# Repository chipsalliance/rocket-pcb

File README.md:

# ROCKET PCB

This project includes the following sub-projects, please read the relevant
documents of sub-projects carefully before starting to use the corresponding
projects.

## FPGA

|            PROJECT         |                     INTRODUCTION                  |
| -------------------------- | ------------------------------------------------- |
| [FPGA_CANDELABRA](./fpga_candelabra) | XCVU13P development board with DDR4, FMC and PCIE |

## FMC

|                 PROJECT                  |          INTRODUCTION          |
| ---------------------------------------- | ------------------------------ |
| [FMC_BASIC_PERI](./fmc_basic_peripheral) | JTAG, UART, GPIO, USB, I3C FMC |
| [FMC_SDRAM](./fmc_sdram)                 | FMC of SDRAM and JTAG          |

## PMOD

|            PROJECT             |      INTRODUCTION      |
| ------------------------------ | ---------------------- |
| [PMOD_MICROSD](./pmod_microsd) | PMOD microSD card slot |
| [PMOD_FT_LINK](./pmod_ft_link/README.md) | FT2232HL USB JTAG and UART adapter for 3.3 V Pmod GPIO ports |

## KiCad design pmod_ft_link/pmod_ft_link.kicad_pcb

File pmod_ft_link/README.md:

# PMOD_FT_LINK

FT-LINK is a USB-to-JTAG and UART adapter built around the FT2232HL. It
connects to a 12-pin Pmod GPIO port with 3.3 V logic. Channel A provides
JTAG through MPSSE; channel B provides UART.

**Keep JP1, marked TIE on the back, open when the host supplies Pmod power.**
The adapter has fixed 3.3 V I/O; it does not sense the target voltage or
translate logic levels. Power the target before driving its signal pins.

## 3D view

### Top view

### Bottom view

## Introduction

### Pmod

The board uses the mechanical dimensions, connector pitch and power-pin
positions of the [Pmod Interface Specification 1.2.0](https://digilent.com/reference/_media/reference/pmod/pmod-interface-specification-1_2_0.pdf).
Its outline is 36.00 × 20.32 mm, with a 1.6 mm thick, two-layer PCB and a
right-angle male connector on 2.54 mm pitch. Specify black solder mask and
white silkscreen on both sides when ordering.

The GPIO assignments below are specific to FT-LINK. This is not an ARM
20-pin or Cortex 10-pin JTAG connector. The FPGA pin constraints and debug
software must use this mapping; a Pmod GPIO port does not automatically
connect to the FPGA's dedicated configuration JTAG chain.

Pmod numbers each six-pin row consecutively. The original FT-LINK drawing
and the VCU118 documentation use alternating odd/even numbering for the
same physical contacts:

| Pmod pin | Original / VCU118 pin | Signal | Direction at FT-LINK | FT2232HL pin |
| --- | --- | --- | --- | --- |
| 1 | 1 | TDO | Input | 18, ADBUS2 |
| 2 | 3 | NTRST | Output, active low | 26, ACBUS0 |
| 3 | 5 | TCK | Output | 16, ADBUS0 |
| 4 | 7 | RXD | Input | 39, BDBUS1 |
| 5 | 9 | GND | Ground | |
| 6 | 11 | PMOD_VCC | Host power rail | |
| 7 | 2 | TDI | Output | 17, ADBUS1 |
| 8 | 4 | TMS | Output | 19, ADBUS3 |
| 9 | 6 | NSRST | Output, active low | 27, ACBUS1 |
| 10 | 8 | TXD | Output | 38, BDBUS0 |
| 11 | 10 | GND | Ground | |
| 12 | 12 | PMOD_VCC | Host power rail | |

Connect TXD to the target's RX input and RXD to its TX output. The JTAG
clock/data signals use the FT2232H MPSSE assignments; the Pmod contact order
is the original FT-LINK order.

### Power and TIE jumper

USB VBUS supplies the FT2232HL through the resettable fuse and AP2112K-3.3
regulator. Pmod pins 6 and 12 are power pins, not VTref inputs. They form the
separate `PMOD_VCC` net while JP1 is open.

JP1 is the original pair of complementary diagonal solder pads, previously
labelled R11 in the source schematic. It is not a resistor or a permanent
net tie. The KiCad symbol is `Jumper:SolderJumper_2_Open`; the custom footprint
is in `CHIPSAlliance_Jumper`. Its copper and stencil shapes follow the
original Gerbers. No component is fitted, so it is excluded from the BOM
and placement files and has no component 3D model.

Bridging JP1 with solder connects USB-derived 3.3 V to the Pmod power rail.
Leave it open for a separately powered host. Closing it requires a deliberate
single-supply arrangement and a verified current budget. An open jumper
isolates the power rails, but does not isolate the signal pins from an
unpowered target.

### Clock

Y1 retains the author's Murata `CSTNE12M0GH5C000R0` ceramic resonator
(LCSC `C2659460`): 12 MHz, 3.2 × 1.3 mm, with two built-in 33 pF capacitors.
There are no added external load capacitors. The `Device:Resonator` symbol
and the CHIPSAlliance footprint retain its three-terminal circuit and the
manufacturer's recommended lands.

Its ±0.07% (±700 ppm) initial tolerance is outside FTDI's recommended
±30 ppm crystal specification. Retaining the original circuit does not
establish compliance with that recommendation, nor prove it cannot work.
Confirm oscillator start-up, frequency over the intended operating range,
and USB operation on assembled hardware before production.

### LEDs

| Reference | Color | Marking / function |
| --- | --- | --- |
| D1 | Red | PWR, USB-derived 3.3 V present |
| D2 | White | TX, driven by FTDI RXLED# |
| D3 | White | RX, driven by FTDI TXLED# |
| D4 | Blue | JTAG, driven by ACBUS3 |

The original TX/RX silkscreen and LED wiring are retained. Their markings
use the opposite perspective to the FTDI RXLED#/TXLED# signal names. JTAG
LED behavior depends on the software's ACBUS3 configuration.

## Preparation

Install KiCad 10, CMake and Ninja, then initialize the pinned library:

```sh
git submodule update --init pmod_ft_link/library
cd pmod_ft_link
```

Open `pmod_ft_link.kicad_pro` in KiCad. The schematic fits one landscape A4
sheet and uses the project's CHIPSAlliance drawing template. Board text
uses embedded Titillium Web Regular; installing the font separately is not
required to view the saved design.

## Build

```sh
cmake -G Ninja -B build
cmake --build build
```

Individual targets are available:

```sh
cmake --build build --target erc drc
cmake --build build --target pdf
cmake --build build --target production
```

Production output contains two-layer Gerbers, separate plated/non-plated
drill files, BOM and SMT placement data. The drill/placement origin is the
lower-left board corner; bottom placement X is negated. Silkscreen export
subtracts solder-mask openings. Generated files stay under `build/`.

J1 is a hybrid USB connector with SMT contacts and plated shield slots;
J2 is through-hole. Both original component placement and signal routing
are retained apart from changes needed for the native footprints and Pmod
mechanics. J1's locating holes use a local 0.10 mm pad-to-hole clearance
matching its land pattern; routed copper retains 0.25 mm hole clearance.

Native DRC retains advisories for the original small regular-weight board
lettering, the intentional negative-text panel, and J1/J2 library-instance
silkscreen adjustments. The generic F1/J2 symbol footprint filters also
produce advisories. These are not hidden. ERC/DRC do not replace hardware
checks of the clock, USB signal integrity, power budget or target compatibility.

## Origin and licenses

Original designer: **-T.K.-**, `t_k_233@outlook.com`, UC Berkeley.
The design comes from [PR #2](https://github.com/chipsalliance/rocket-pcb/pull/2),
source commit `8a24312734b0e4b31bfd77401dffb280b939f82e`.
The title blocks retain the original schematic date **2024-02-29**, PCB date
**2024-03-20**, and revision **V2.0.0**.

The native KiCad migration preserves the circuit, artwork and clock choice,
uses standard or CHIPSAlliance library assets, and renames the solder bridge
from R11 to JP1. The original artwork remains editable vector geometry;
the board lettering uses native editable text. No EasyEDA source archives,
manufacturing outputs or review reports are required in this directory.

The source font name was `ACME Titillium Web Regular`. Board lettering now
uses the unmodified [Titillium Web Regular font from Google Fonts](https://github.com/google/fonts/tree/main/ofl/titilliumweb),
embedded in `pmod_ft_link.kicad_pcb`. Its copyright notice and full SIL Open
Font License 1.1 are in [licenses/TitilliumWeb-OFL.txt](./licenses/TitilliumWeb-OFL.txt).
The OFL permits commercial design use and embedding under its distribution
conditions. The ACME font binary is not redistributed. Library reference
and fabrication fields retain KiCad's default font, as required by KLC.

## References

- [FT2232H datasheet, oscillator section 6.3](https://ftdichip.com/wp-content/uploads/2024/05/DS_FT2232H.pdf)
- [Murata CSTNE12M0GH5C000R0 specification](https://www.murata.com/products/productdata/8801162100766/SPEC-CSTNE12M0GH5C000R0.pdf)
- [Kinghelm KH-TYPE-C-16P drawing](https://www.kinghelm.com.cn/upload/file/20220505/KH-TYPE-C-16P.pdf)

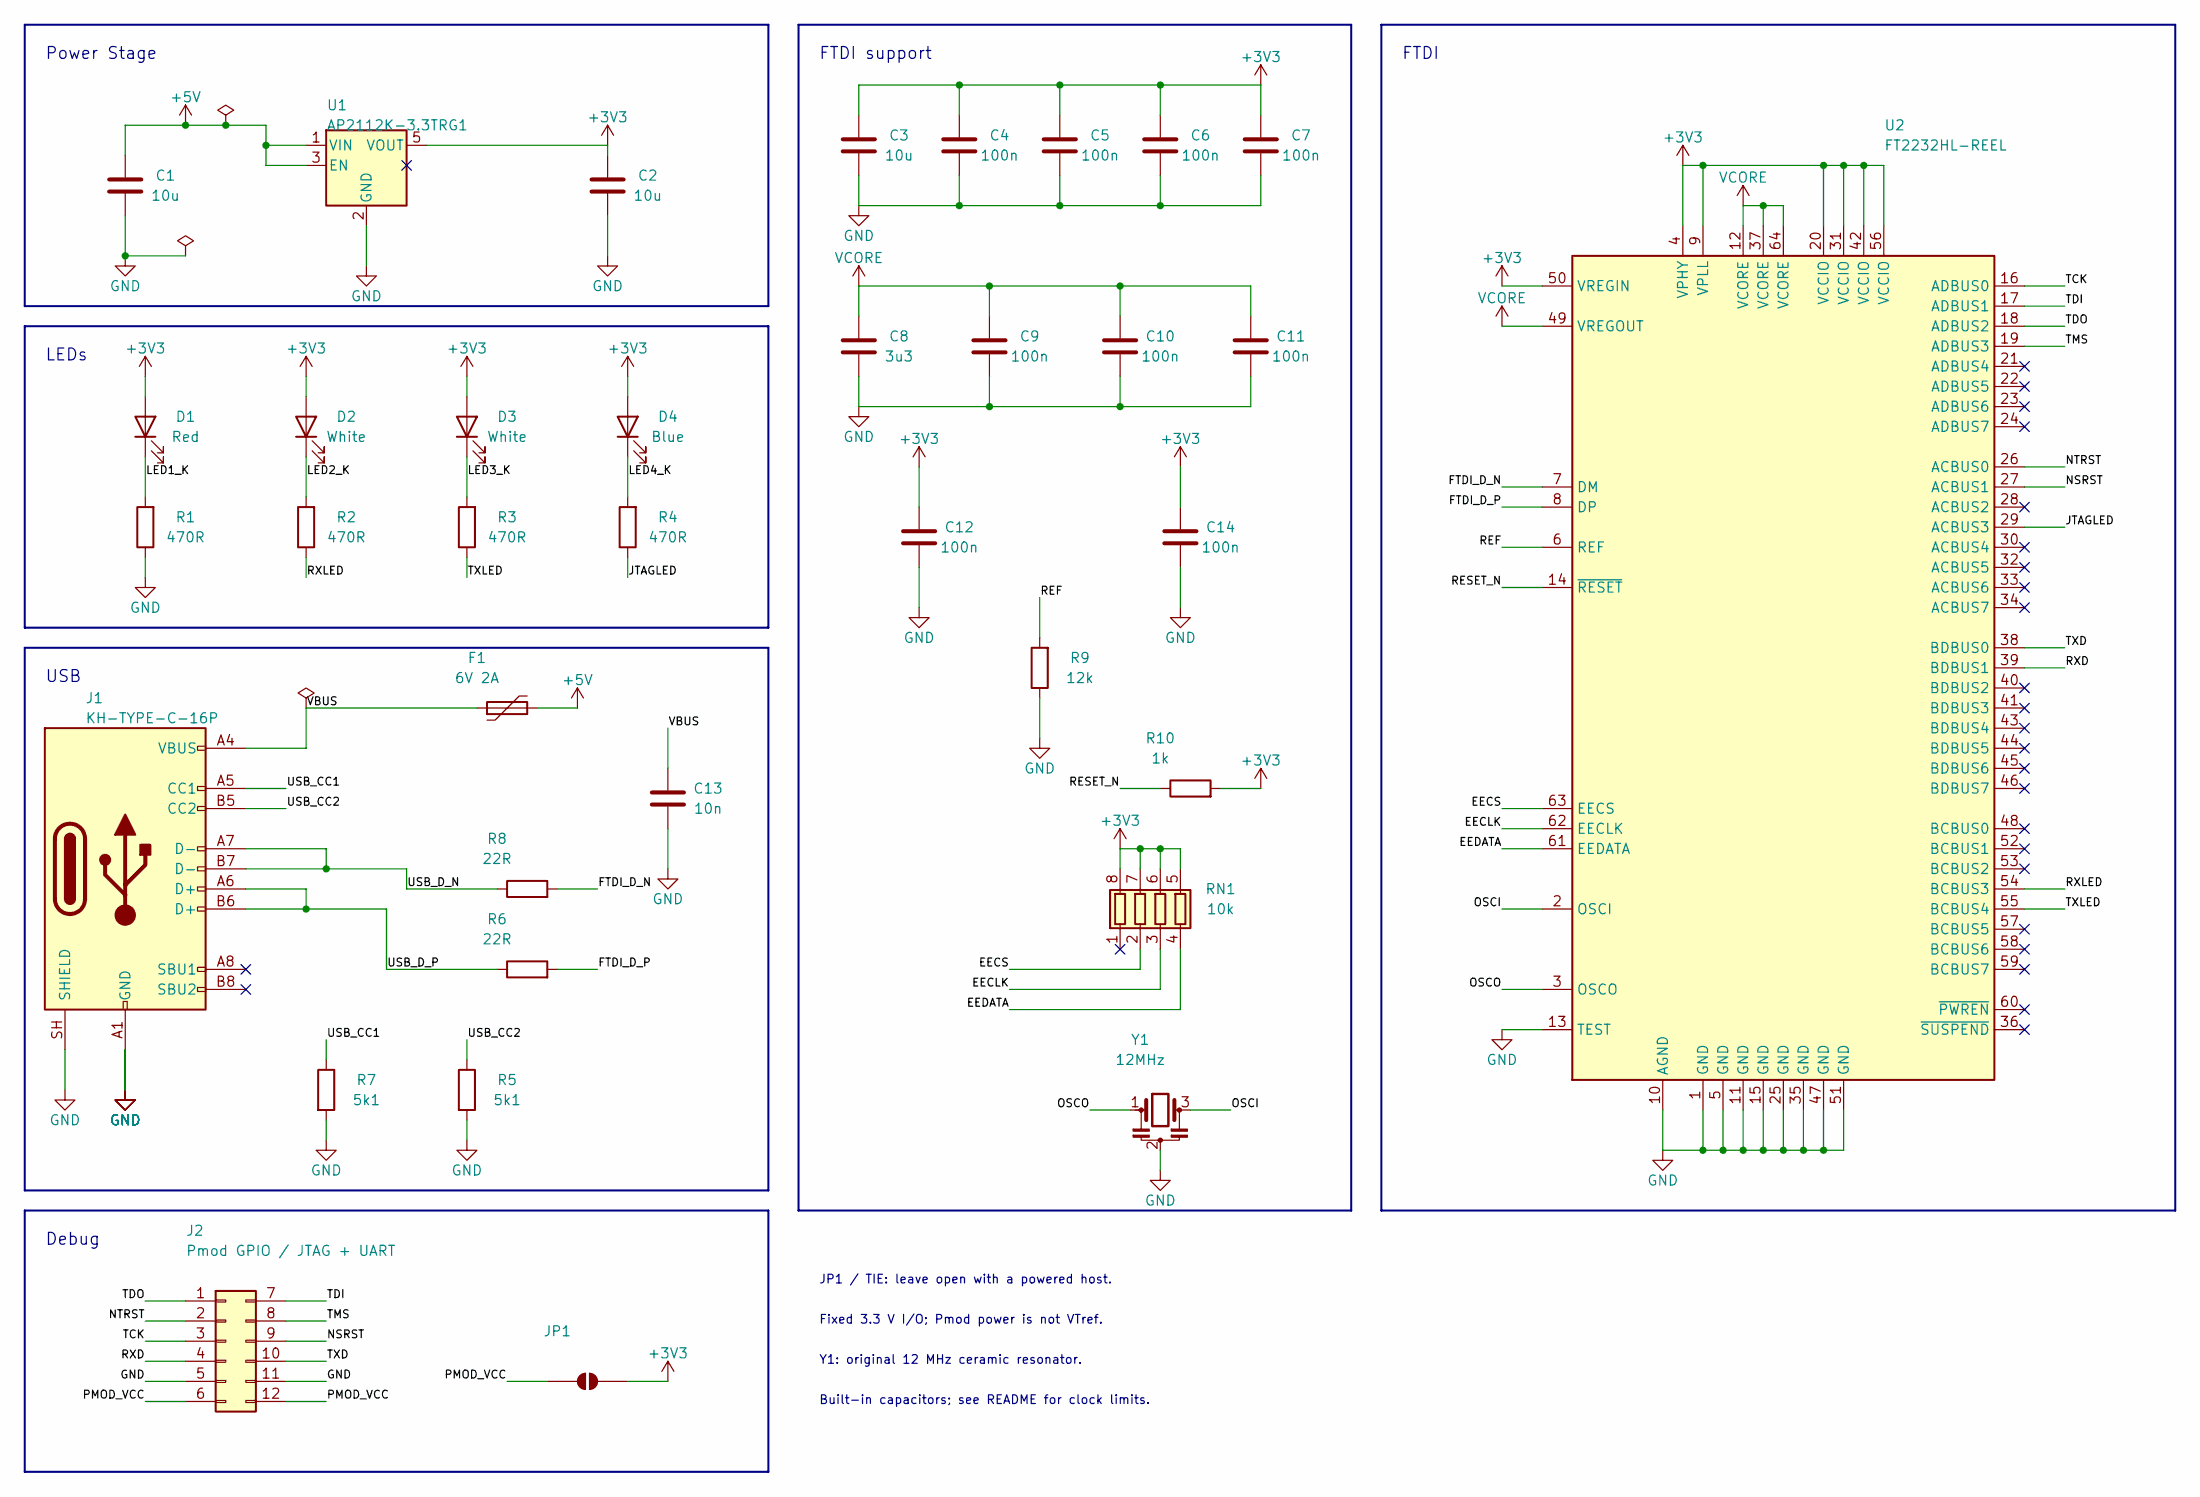
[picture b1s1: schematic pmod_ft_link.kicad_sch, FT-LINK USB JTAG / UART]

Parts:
C1, C2, C3: 10u; C_0603_1608Metric; MPN CL10A106KP8NNNC; LCSC C19702
C4, C5, C6, C7, C9, C10, C11, C12, C14: 100n; C_0402_1005Metric; MPN CL05B104KB54PNC; LCSC C307331
C8: 3u3; C_0603_1608Metric; MPN C1608X5R1E335KT000E; LCSC C342962
C13: 10n; C_0402_1005Metric; MPN CL05B103KB5NNNC; LCSC C15195
D1: Red; LED_0603_1608Metric; MPN 19-217/R6C-AL1M2VY/3T; LCSC C72044
D2, D3: White; LED_0603_1608Metric; MPN LED White; LCSC C2290
D4: Blue; LED_0603_1608Metric; MPN XL-0603QBC; LCSC C2288
F1: 6V 2A; Fuse_0805_2012Metric; MPN SL0805200; LCSC C70158
J1: KH-TYPE-C-16P; USB_C_Receptacle_Kinghelm_KH-TYPE-C-16P; MPN KH-TYPE-C-16P; LCSC C709357
J2: Pmod GPIO / JTAG + UART; PinHeader_2x06_P2.54mm_Horizontal_PMOD; MPN A2541WR-2x6P; LCSC C239337
JP1: SolderJumper_2_Open; SolderJumper-2_P0.713mm_Open_DiagonalPads
R1, R2, R3, R4: 470R; R_0402_1005Metric; MPN 0402WGF4700TCE; LCSC C25117
R5, R7: 5k1; R_0402_1005Metric; MPN 0402WGF5101TCE; LCSC C25905
R6, R8: 22R; R_0402_1005Metric; MPN 0402WGF220JTCE; LCSC C25092
R9: 12k; R_0402_1005Metric; MPN 0402WGF1202TCE; LCSC C25752
R10: 1k; R_0402_1005Metric; MPN 0402WGF1001TCE; LCSC C11702
RN1: 10k; R_Array_Convex_4x0402; MPN YC124-FR-0710KL; LCSC C136853
U1: AP2112K-3.3TRG1; SOT-23-5; MPN AP2112K-3.3TRG1; LCSC C51118
U2: FT2232HL-REEL; LQFP-64_10x10mm_P0.5mm; MPN FT2232HL-REEL; LCSC C27882
Y1: 12MHz; Resonator_SMD_Murata_CSTNE-3Pin_3.2x1.3mm; MPN CSTNE12M0GH5C000R0; LCSC C2659460

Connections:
+3V3: C2.2, C3.2, C4.2, C5.2, C6.2, C7.2, C12.2, C14.2, D1.2 (A), D2.2 (A), D3.2 (A), D4.2 (A), JP1.2 (B), R10.2, RN1.5 (R4.2), RN1.6 (R3.2), RN1.7 (R2.2), RN1.8 (R1.2), U1.5 (VOUT), U2.4 (VPHY), U2.9 (VPLL), U2.20 (VCCIO), U2.31 (VCCIO), U2.42 (VCCIO), U2.50 (VREGIN), U2.56 (VCCIO)
+5V: C1.2, F1.2, U1.1 (VIN), U1.3 (EN)
/EECLK: RN1.3 (R3.1), U2.62 (EECLK)
/EECS: RN1.2 (R2.1), U2.63 (EECS)
/EEDATA: RN1.4 (R4.1), U2.61 (EEDATA)
/FTDI_D_N: R8.2, U2.7 (DM)
/FTDI_D_P: R6.2, U2.8 (DP)
/JTAGLED: R4.1, U2.29 (ACBUS3)
/LED1_K: D1.1 (K), R1.2
/LED2_K: D2.1 (K), R2.2
/LED3_K: D3.1 (K), R3.2
/LED4_K: D4.1 (K), R4.2
/NSRST: J2.9, U2.27 (ACBUS1)
/NTRST: J2.2, U2.26 (ACBUS0)
/OSCI: U2.2 (OSCI), Y1.3
/OSCO: U2.3 (OSCO), Y1.1
/PMOD_VCC: J2.6, J2.12, JP1.1 (A)
/REF: R9.2, U2.6 (REF)
/RESET_N: R10.1, U2.14 (~RESET)
/RXD: J2.4, U2.39 (BDBUS1)
/RXLED: R2.1, U2.54 (BCBUS3)
/TCK: J2.3, U2.16 (ADBUS0)
/TDI: J2.7, U2.17 (ADBUS1)
/TDO: J2.1, U2.18 (ADBUS2)
/TMS: J2.8, U2.19 (ADBUS3)
/TXD: J2.10, U2.38 (BDBUS0)
/TXLED: R3.1, U2.55 (BCBUS4)
/USB_CC1: J1.A5 (CC1), R7.1
/USB_CC2: J1.B5 (CC2), R5.1
/USB_D_N: J1.A7 (D-), J1.B7 (D-), R8.1
/USB_D_P: J1.A6 (D+), J1.B6 (D+), R6.1
/VBUS: C13.2, F1.1, J1.A4 (VBUS), J1.A9 (VBUS), J1.B4 (VBUS), J1.B9 (VBUS)
GND: C1.1, C2.1, C3.1, C4.1, C5.1, C6.1, C7.1, C8.2, C9.1, C10.1, C11.1, C12.1, C13.1, C14.1, J1.A1 (GND), J1.A12 (GND), J1.B1 (GND), J1.B12 (GND), J1.SH (SHIELD), J2.5, J2.11, R1.1, R5.2, R7.2, R9.1, U1.2 (GND), U2.1 (GND), U2.5 (GND), U2.10 (AGND), U2.11 (GND), U2.13 (TEST), U2.15 (GND), U2.25 (GND), U2.35 (GND), U2.47 (GND), U2.51 (GND), Y1.2
VCORE: C8.1, C9.2, C10.2, C11.2, U2.12 (VCORE), U2.37 (VCORE), U2.49 (VREGOUT), U2.64 (VCORE)

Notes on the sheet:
Fixed 3.3 V I/O; Pmod power is not VTref.
LEDs
FTDI
JP1 / TIE: leave open with a powered host.
Y1: original 12 MHz ceramic resonator.
Built-in capacitors; see README for clock limits.
Debug
USB
Power Stage
FTDI support

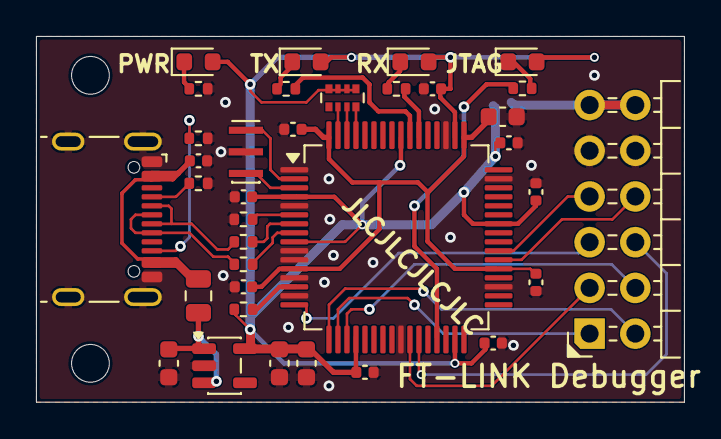
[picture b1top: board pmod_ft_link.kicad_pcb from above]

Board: 2 copper layers, 36.0 x 20.3 mm, 38 parts (1 on the bottom side), 34 nets.

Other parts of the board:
H1, H2: MountingHole; MountingHole_2.1mm

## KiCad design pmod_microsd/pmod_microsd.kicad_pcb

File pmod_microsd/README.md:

# PMOD_MICROSD

The Pmod MicroSD provides a microSD card slot to any board that has 3.3V logic
and is pin compatible with a 12-pin Pmod port capable of SPI communication.

This board is specially designed to adapt to VCU118, and the pull-up resistor
for SDIO is modified to 330 ohm.

## 3D view

### Top view

### Bottom view

## Introduction

### PMOD

This design complies with [Digilent Pmod™ Interface Specification 1.2.0](https://digilent.com/reference/_media/reference/pmod/pmod-interface-specification-1_2_0.pdf).

Note that the pin sequence numbers on the digilent PMOD specification are
inconsistent with the PMOD pin sequence numbers of AMD VCU118 on the document.
Essentially they are the same, but the numbering of AMD VCU118 uses a
double-column staggered odd-even arrangement.
Here is their mapping relationship.

| PMOD PIN | VCU118 PIN | SDIO FUNCTION | SPI FUNCTION |
| -------- | ---------- | ------------- | ------------ |
| 1        | 1          | DAT3(D3)      | #CS          |
| 2        | 3          | CMD           | MOSI         |
| 3        | 5          | DAT0(D0)      | MISO         |
| 4        | 7          | CLK           | SCLK(SCK)    |
| 5        | 9          | GND           | GND          |
| 6        | 11         | 3P3V(VDD)     | 3P3V(VDD)    |
| 7        | 2          | DAT1(D1)      | NC           |
| 8        | 4          | DAT2(D2)      | NC           |
| 9        | 6          | #DET(#CD)     | #DET(#CD)    |
| 10       | 8          | #WP           | #WP          |
| 11       | 10         | GND           | GND          |
| 12       | 12         | 3P3V(VDD)     | 3P3V(VDD)    |

### LED

There are two LEDs on the PCB, the yellow one is the card detection indicator
and the orange one is the power indicator.

| LED | COLOR  |         FUNCTION         |          ON           |       OFF       |
| --- | ------ | ------------------------ | --------------------- | --------------- |
| 1   | Yellow | Card detection indicator | MicroSD Card inserted | No MicroSD card |
| 2   | Orange | Power indicator          | Power on              | Power off       |

### Special signal

Among them, the ``#WP`` signal is constant high level. If the ``WP`` signal is
low, please check the power supply and there may be a fault.

|   NAME    |         HIGH         |           LOW            |
| --------- | -------------------- | ------------------------ |
| #DET(#CD) | No MicroSD card      | MicroSD Card inserted    |
| #WP       | Write protect is off | This state is impossible |

## Preparation

Install kicad 8, cmake, ninja.

## Build

```bash
cmake -G Ninja -B build
cmake --build build
```

If you only need to generate a pdf of the schematic or pcb,

```bash
cmake --build build --target pdf
```

If you need to generate complete production data,

```bash
cmake --build build --target production
```

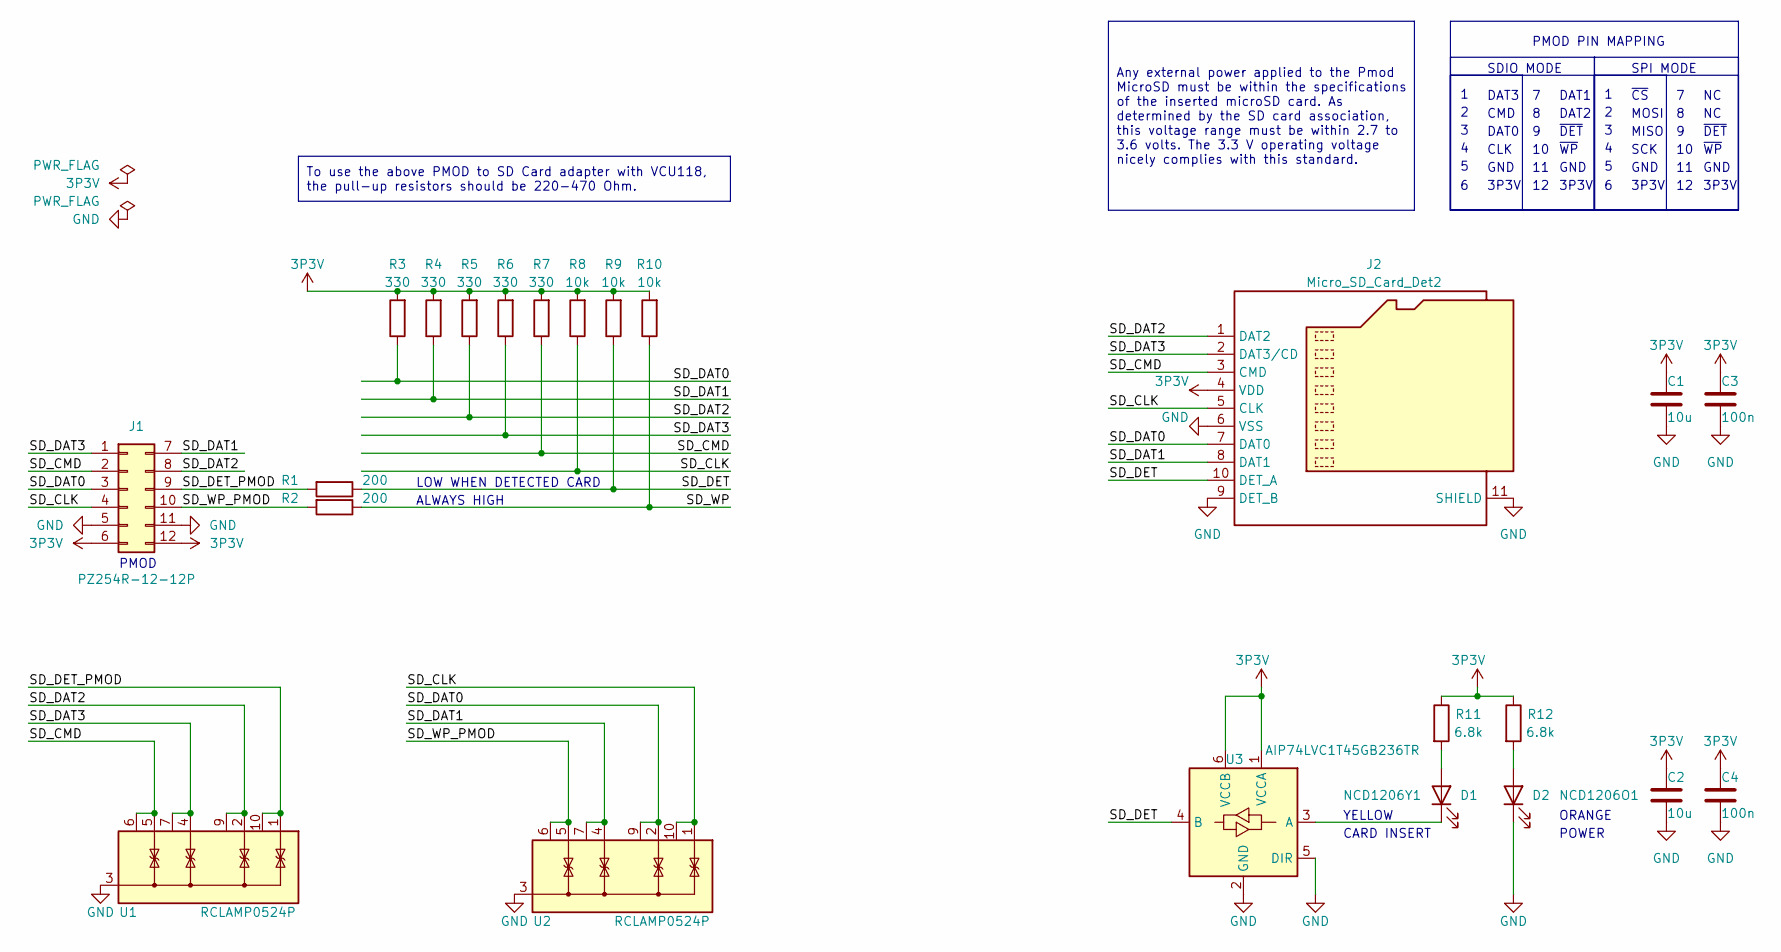
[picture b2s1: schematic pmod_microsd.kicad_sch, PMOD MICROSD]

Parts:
C1, C2: 10u; C_0402_1005Metric
C3, C4: 100n; C_0402_1005Metric
D1: NCD1206Y1; LED_1206_3216Metric
D2: NCD1206O1; LED_1206_3216Metric
J1: PZ254R-12-12P; PinHeader_2x06_P2.54mm_Horizontal_PMOD
J2: Micro_SD_Card_Det2; microSD_HC_Molex_104031-0811
R1, R2: 200; R_0402_1005Metric
R3, R4, R5, R6, R7: 330; R_0402_1005Metric
R8, R9, R10: 10k; R_0402_1005Metric
R11, R12: 6.8k; R_0402_1005Metric
U1, U2: RCLAMP0524P; USON-10_2.5x1.0mm_P0.5mm
U3: AIP74LVC1T45GB236TR; SOT-23-6; JLCPCB Rotation Offset -180

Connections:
3P3V: C1.1, C2.1, C3.1, C4.1, J1.6, J1.12, J2.4 (VDD), R3.2, R4.2, R5.2, R6.2, R7.2, R8.2, R9.2, R10.2, R11.1, R12.1, U3.1 (VCCA), U3.6 (VCCB)
/SD_CLK: J1.4, J2.5 (CLK), R8.1, U2.1 (IO1), U2.10 (NC)
/SD_CMD: J1.2, J2.3 (CMD), R7.1, U1.5 (IO4), U1.6 (NC)
/SD_DAT0: J1.3, J2.7 (DAT0), R3.1, U2.2 (IO2), U2.9 (NC)
/SD_DAT1: J1.7, J2.8 (DAT1), R4.1, U2.4 (IO3), U2.7 (NC)
/SD_DAT2: J1.8, J2.1 (DAT2), R5.1, U1.2 (IO2), U1.9 (NC)
/SD_DAT3: J1.1, J2.2 (DAT3/CD), R6.1, U1.4 (IO3), U1.7 (NC)
/SD_DET: J2.10 (DET_A), R1.1, R9.1, U3.4 (B)
/SD_DET_PMOD: J1.9, R1.2, U1.1 (IO1), U1.10 (NC)
/SD_WP: R2.1, R10.1
/SD_WP_PMOD: J1.10, R2.2, U2.5 (IO4), U2.6 (NC)
GND: C1.2, C2.2, C3.2, C4.2, D2.1 (K), J1.5, J1.11, J2.6 (VSS), J2.9 (DET_B), J2.11 (SHIELD), U1.3 (G), U1.8 (G), U2.3 (G), U2.8 (G), U3.2 (GND), U3.5 (DIR)
unnamed: D1.2 (A), R11.2
unnamed: D1.1 (K), U3.3 (A)
unnamed: D2.2 (A), R12.2

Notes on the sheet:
Any external power applied to the Pmod MicroSD must be within the specifications of the inserted microSD card. As determined by the SD card association, this voltage range must be within 2.7 to 3.6 volts. The 3.3 V operating voltage nicely complies with this standard.
To use the above PMOD to SD Card adapter with VCU118, the pull-up resistors should be 220-470 Ohm.
~{CS}
POWER
SPI MODE
~{DET}
GND
3P3V
ORANGE
CARD INSERT
DAT0
MISO
LOW WHEN DETECTED CARD
DAT3
PMOD
YELLOW
SDIO MODE
CLK
~{WP}
DAT2
DAT1
CMD
MOSI
SCK
PMOD PIN MAPPING
ALWAYS HIGH

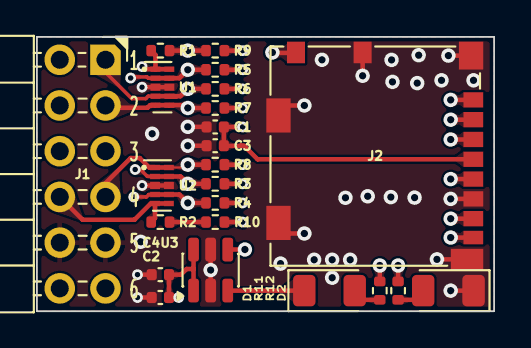
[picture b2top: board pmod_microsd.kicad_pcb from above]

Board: 4 copper layers, 25.4 x 15.2 mm, 23 parts (0 on the bottom side), 15 nets.

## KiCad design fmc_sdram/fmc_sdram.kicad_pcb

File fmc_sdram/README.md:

# FMC_SDRAM

FMC mezannine card with dual MT48LC16M16A2 SDRAM, organized as 16Mx32bit, with level shifters for VADJ.
Also includes USB to UART bridge, JTAG level shifter with ARM 20-pin JTAG header.

## Preparation

Install kicad 10, cmake, ninja, frugy.

## Precautions

When using it for the first time, it is necessary to program the IPMI FRU data
for the EEPROM so that the development board can identify the power supply
of the FMC.

## Build

```bash
cmake -G Ninja -B build
cmake --build build
```

If you only need to build the eeprom binary,

```bash
cmake --build build --target eeprom
```

If you only need to generate a pdf of the schematic or pcb,

```bash
cmake --build build --target pdf
```

If you need to generate complete production data,

```bash
cmake --build build --target production
```

## Program the FRU EEPROM

Use a CH341A USB-to-I2C adapter (PID `1a86:5512`, EPP/MEM/I2C mode) with
[ch341eeprom](https://github.com/commandtab/ch341eeprom). Wire `SDA`, `SCL`,
`VCC` (3.3V) and `GND` to the on-board M24C02, and pull `WP` to GND.

```bash
ch341eeprom -s 24c02 -e
ch341eeprom -s 24c02 -w build/fmc_fru_eeprom.bin
ch341eeprom -s 24c02 -V build/fmc_fru_eeprom.bin
```

`ch341eeprom` truncates the 2 KiB bin to the 256-byte chip on write, and the
verifier passes end-to-end. To inspect the FRU contents semantically,
`ch341eeprom -s 24c02 -r /tmp/dump.bin && frugy -r -d /tmp/dump.bin`.

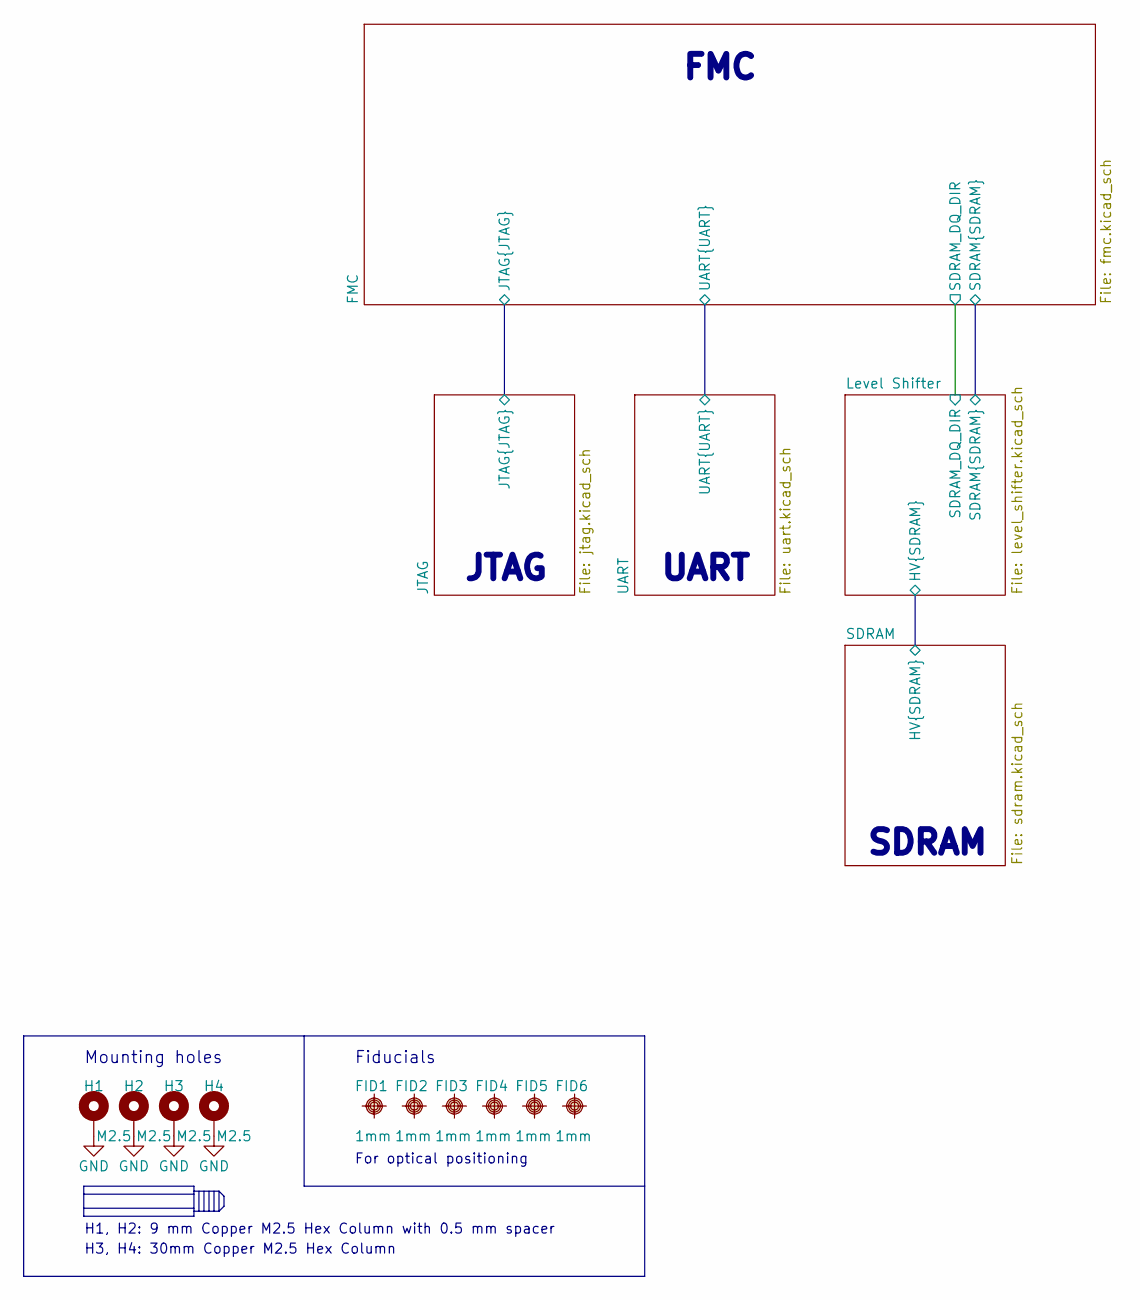
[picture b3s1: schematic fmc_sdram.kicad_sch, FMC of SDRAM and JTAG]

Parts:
FID1, FID2, FID3, FID4, FID5, FID6: 1mm; Fiducial_1mm_Mask2mm
H1, H2: M2.5; MountingHole_2.7mm_M2.5_FMC_Pad_Via
H3, H4: M2.5; MountingHole_2.7mm_M2.5_FMC_Pad

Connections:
GND: H1.1 (1_1), H2.1 (1_1), H3.1 (1_1), H4.1 (1_1); also elsewhere on the board

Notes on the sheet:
H1, H2: 9 mm Copper M2.5 Hex Column with 0.5 mm spacer
For optical positioning
Fiducials
FMC
UART
JTAG
H3, H4: 30mm Copper M2.5 Hex Column
Mounting holes
SDRAM

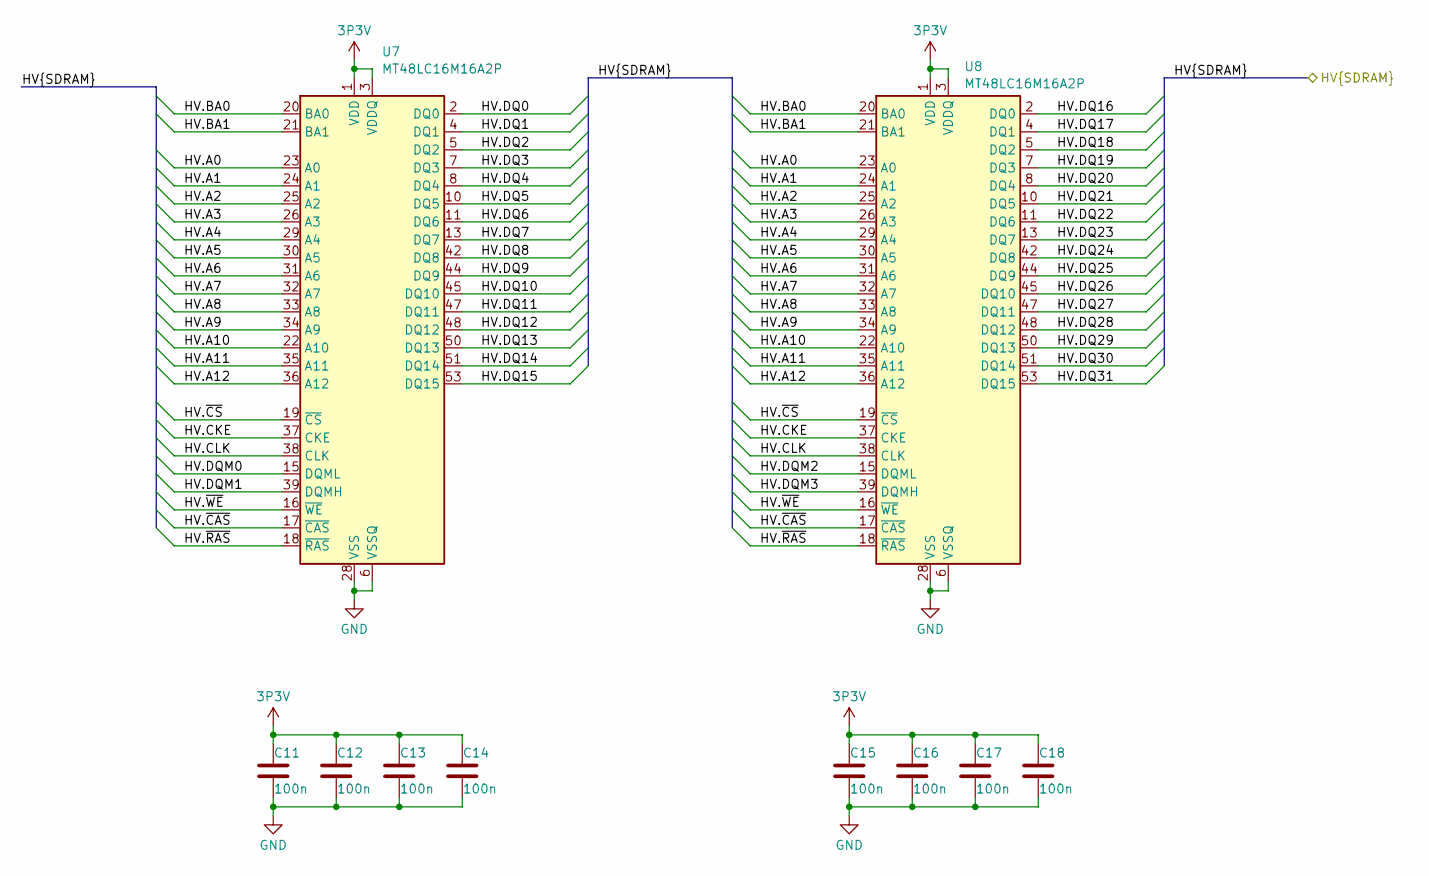
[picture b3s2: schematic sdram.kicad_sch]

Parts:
C11, C12, C13, C14, C15, C16, C17, C18: 100n; C_0402_1005Metric
U7, U8: MT48LC16M16A2P; TSOP-II-54_22.2x10.16mm_P0.8mm

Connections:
3P3V: C11.1, C12.1, C13.1, C14.1, C15.1, C16.1, C17.1, C18.1, U7.1 (VDD), U7.3 (VDDQ), U7.9 (VDDQ), U7.14 (VDD), U7.27 (VDD), U7.43 (VDDQ), U7.49 (VDDQ), U8.1 (VDD), U8.3 (VDDQ), U8.9 (VDDQ), U8.14 (VDD), U8.27 (VDD), U8.43 (VDDQ), U8.49 (VDDQ); also elsewhere on the board
/Level Shifter/HV.A0: U7.23 (A0), U8.23 (A0); also elsewhere on the board
/Level Shifter/HV.A1: U7.24 (A1), U8.24 (A1); also elsewhere on the board
/Level Shifter/HV.A2: U7.25 (A2), U8.25 (A2); also elsewhere on the board
/Level Shifter/HV.A3: U7.26 (A3), U8.26 (A3); also elsewhere on the board
/Level Shifter/HV.A4: U7.29 (A4), U8.29 (A4); also elsewhere on the board
/Level Shifter/HV.A5: U7.30 (A5), U8.30 (A5); also elsewhere on the board
/Level Shifter/HV.A6: U7.31 (A6), U8.31 (A6); also elsewhere on the board
/Level Shifter/HV.A7: U7.32 (A7), U8.32 (A7); also elsewhere on the board
/Level Shifter/HV.A8: U7.33 (A8), U8.33 (A8); also elsewhere on the board
/Level Shifter/HV.A9: U7.34 (A9), U8.34 (A9); also elsewhere on the board
/Level Shifter/HV.A10: U7.22 (A10), U8.22 (A10); also elsewhere on the board
/Level Shifter/HV.A11: U7.35 (A11), U8.35 (A11); also elsewhere on the board
/Level Shifter/HV.A12: U7.36 (A12), U8.36 (A12); also elsewhere on the board
/Level Shifter/HV.BA0: U7.20 (BA0), U8.20 (BA0); also elsewhere on the board
/Level Shifter/HV.BA1: U7.21 (BA1), U8.21 (BA1); also elsewhere on the board
/Level Shifter/HV.CKE: U7.37 (CKE), U8.37 (CKE); also elsewhere on the board
/Level Shifter/HV.CLK: U7.38 (CLK), U8.38 (CLK); also elsewhere on the board
/Level Shifter/HV.DQ0: U7.2 (DQ0); also elsewhere on the board
/Level Shifter/HV.DQ1: U7.4 (DQ1); also elsewhere on the board
/Level Shifter/HV.DQ2: U7.5 (DQ2); also elsewhere on the board
/Level Shifter/HV.DQ3: U7.7 (DQ3); also elsewhere on the board
/Level Shifter/HV.DQ4: U7.8 (DQ4); also elsewhere on the board
/Level Shifter/HV.DQ5: U7.10 (DQ5); also elsewhere on the board
/Level Shifter/HV.DQ6: U7.11 (DQ6); also elsewhere on the board
/Level Shifter/HV.DQ7: U7.13 (DQ7); also elsewhere on the board
/Level Shifter/HV.DQ8: U7.42 (DQ8); also elsewhere on the board
/Level Shifter/HV.DQ9: U7.44 (DQ9); also elsewhere on the board
/Level Shifter/HV.DQ10: U7.45 (DQ10); also elsewhere on the board
/Level Shifter/HV.DQ11: U7.47 (DQ11); also elsewhere on the board
/Level Shifter/HV.DQ12: U7.48 (DQ12); also elsewhere on the board
/Level Shifter/HV.DQ13: U7.50 (DQ13); also elsewhere on the board
/Level Shifter/HV.DQ14: U7.51 (DQ14); also elsewhere on the board
/Level Shifter/HV.DQ15: U7.53 (DQ15); also elsewhere on the board
/Level Shifter/HV.DQ16: U8.2 (DQ0); also elsewhere on the board
/Level Shifter/HV.DQ17: U8.4 (DQ1); also elsewhere on the board
/Level Shifter/HV.DQ18: U8.5 (DQ2); also elsewhere on the board
/Level Shifter/HV.DQ19: U8.7 (DQ3); also elsewhere on the board
/Level Shifter/HV.DQ20: U8.8 (DQ4); also elsewhere on the board
/Level Shifter/HV.DQ21: U8.10 (DQ5); also elsewhere on the board
/Level Shifter/HV.DQ22: U8.11 (DQ6); also elsewhere on the board
/Level Shifter/HV.DQ23: U8.13 (DQ7); also elsewhere on the board
/Level Shifter/HV.DQ24: U8.42 (DQ8); also elsewhere on the board
/Level Shifter/HV.DQ25: U8.44 (DQ9); also elsewhere on the board
/Level Shifter/HV.DQ26: U8.45 (DQ10); also elsewhere on the board
/Level Shifter/HV.DQ27: U8.47 (DQ11); also elsewhere on the board
/Level Shifter/HV.DQ28: U8.48 (DQ12); also elsewhere on the board
/Level Shifter/HV.DQ29: U8.50 (DQ13); also elsewhere on the board
/Level Shifter/HV.DQ30: U8.51 (DQ14); also elsewhere on the board
/Level Shifter/HV.DQ31: U8.53 (DQ15); also elsewhere on the board
/Level Shifter/HV.DQM0: U7.15 (DQML); also elsewhere on the board
/Level Shifter/HV.DQM1: U7.39 (DQMH); also elsewhere on the board
/Level Shifter/HV.DQM2: U8.15 (DQML); also elsewhere on the board
/Level Shifter/HV.DQM3: U8.39 (DQMH); also elsewhere on the board
/Level Shifter/HV.~CAS: U7.17 (~CAS), U8.17 (~CAS); also elsewhere on the board
/Level Shifter/HV.~CS: U7.19 (~CS), U8.19 (~CS); also elsewhere on the board
/Level Shifter/HV.~RAS: U7.18 (~RAS), U8.18 (~RAS); also elsewhere on the board
/Level Shifter/HV.~WE: U7.16 (~WE), U8.16 (~WE); also elsewhere on the board
GND: C11.2, C12.2, C13.2, C14.2, C15.2, C16.2, C17.2, C18.2, U7.6 (VSSQ), U7.12 (VSSQ), U7.28 (VSS), U7.41 (VSS), U7.46 (VSSQ), U7.52 (VSSQ), U7.54 (VSS), U8.6 (VSSQ), U8.12 (VSSQ), U8.28 (VSS), U8.41 (VSS), U8.46 (VSSQ), U8.52 (VSSQ), U8.54 (VSS); also elsewhere on the board

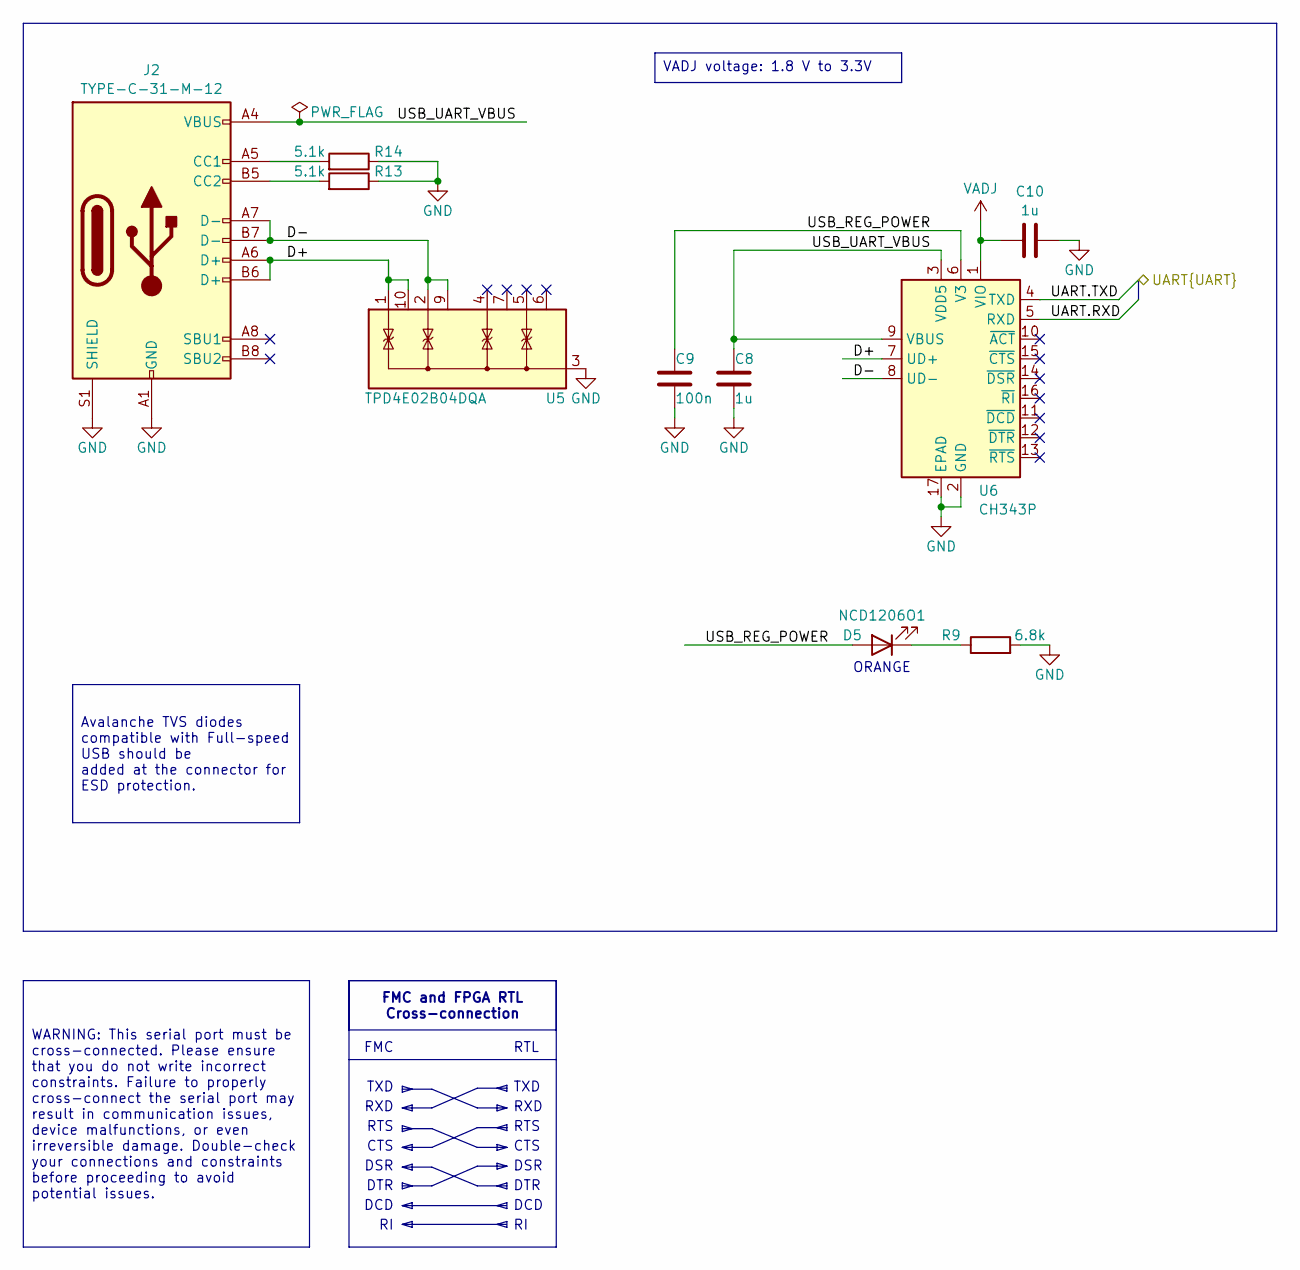
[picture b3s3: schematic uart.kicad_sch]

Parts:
C8, C10: 1u; C_0402_1005Metric
C9: 100n; C_0402_1005Metric
D5: NCD1206O1; LED_1206_3216Metric
J2: TYPE-C-31-M-12; USB_C_Receptacle_HRO_TYPE-C-31-M-12
R9: 6.8k; R_0402_1005Metric
R13, R14: 5.1k; R_0402_1005Metric
U5: TPD4E02B04DQA; USON-10_2.5x1.0mm_P0.5mm
U6: CH343P; QFN-16-1EP_3x3mm_P0.5mm_EP1.7x1.7mm

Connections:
/FMC/UART.RXD: U6.5 (RXD); also elsewhere on the board
/FMC/UART.TXD: U6.4 (TXD); also elsewhere on the board
/UART/D+: J2.A6 (D+), J2.B6 (D+), U5.1 (IO1), U5.10 (NC), U6.7 (UD+)
/UART/D-: J2.A7 (D-), J2.B7 (D-), U5.2 (IO2), U5.9 (NC), U6.8 (UD-)
/UART/USB_REG_POWER: C9.1, D5.2 (A), U6.6 (V3)
/UART/USB_UART_VBUS: C8.1, J2.A4 (VBUS), J2.A9 (VBUS), J2.B4 (VBUS), J2.B9 (VBUS), U6.3 (VDD5), U6.9 (VBUS)
GND: C8.2, C9.2, C10.2, J2.A1 (GND), J2.A12 (GND), J2.B1 (GND), J2.B12 (GND), J2.S1 (SHIELD), R9.2, R13.1, R14.1, U5.3 (G), U5.8 (G), U6.2 (GND), U6.17 (EPAD); also elsewhere on the board
unnamed: D5.1 (K), R9.1
unnamed: J2.A5 (CC1), R14.2
unnamed: J2.B5 (CC2), R13.2
VADJ: C10.1, U6.1 (VIO); also elsewhere on the board

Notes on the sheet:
ORANGE
FMC
RXD
TXD
DCD
RTS
DSR
DTR
CTS
RTL
FMC and FPGA RTL Cross-connection
WARNING: This serial port must be cross-connected. Please ensure that you do not write incorrect constraints. Failure to properly cross-connect the serial port may result in communication issues, device malfunctions, or even irreversible damage. Double-check your connections and constraints before 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
VADJ voltage: 1.8 V to 3.3V
Avalanche TVS diodes compatible with Full-speed USB should be added at the connector for ESD protection.
